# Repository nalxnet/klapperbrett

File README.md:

# klapperbrett

Die Klappenanzeige (Salzkotten EC2000-FP6) stammt aus einer Zapfsäule und zeigte die üblichen Werte (Literpreis, Gesamtmenge, Gesamtpreis) an.

Es sind drei Anschlüsse vorhanden:
* Pfostenstecker 10-polig, von außen zugänglich: vmtl. Anschluss an den Rest der Zapfsäule, inkl. Stromversorgung (2 Pins +24V, 2 Pins GND).
* Pfostenstecker 12-polig(?), nur von innen zugänglich: vmtl. Service-Anschluss zur Neuprogrammierung, kein +24V oder +5V, nur GND.
* 2 Bohrungen für +24V und GND, nicht verlötet.

Steuerung erfolgt original über einen 8-bit Mikrocontroller, der in einen 40-pol. IC-Sockel gesteckt ist. Hier setzen wir an und ersetzen diesen mit einem Arduino/ESP.

Es gibt 3 Zeilen, die oberen beiden haben 5 Elemente, die unterste hat 4. Jedes Element hat 7 Segmente zur Anzeige einer Zahl. Logisch sind zur Ansteuerung alle Elemente in einer Reihe aufgebaut, dadurch lassen sich die einzelnen Segmente als Matrix darstellen, wobei die Elemente die Spalten und die Segmente die Zeilen darstellen. Jedes Segment besteht aus einem Elektromagneten, der je nach Stromfluss anders polarisiert ist und dadurch das Segment in An- bzw. Aus-Position bewegt. Dafür ist eine Seite der Spule direkt an die Spaltenleitung angeschlossen. Die andere Seite der Spule ist mit jeweils einer Diode an zwei Elementleitungen angeschlossen. Eine zum Bewegen in An-Position, die andere für die Aus-Position.

Die Ansteuerung der einzelnen Segmente übernehmen zwei FP2800A. Der obere (FPZ) steuert die Zeilen, der untere (FPS) die Spalten.

Pinbelegung Mikrocontroller (alle nicht aufgeführten sind unbekannt):
```
1: FPS A0
2: FPS A1
3: FPS A2
4: FPS B0
5: FPS B1
6: (über JP1 an PCF8582C-2 Pin SDA --> I2C)
7: FPS ENABLE
...
20: GND
33: FPZ ENABLE
34: FPZ B0, FPZ DATA, FPS DATA
35: FPZ B1
...
37: FPZ A2
38: FPZ A1
39: FPZ A0
40: +5V
```

Ansteuerung der Segmente erfolgt durch Setzen der Spalten- und Zeilenadresse (je 8 Bit), DATA wird durch invertierenden Schmitt-Trigger bereits passend gesetzt. Um das Segment zu schalten muss abschließend ein kurzer Puls an beiden ENABLE-Pins gleichzeitig (HIGH nach LOW) erfolgen, für dessen Zeit die Spalten- und Zeilenleitung tatsächlich gesetzt wird.

Adressierung der Elemente erfolgt von oben nach unten, von rechts nach links. Freie Element-Plätze sind ebenfalls adressiert, 8 und 16 werden übersprungen.

```
 6  5  4  3  2  1

13 12 11 10  9  7

   19 18 17 15 14
```

Die Adressierung der Segmente erfolgt gegen den Uhrzeigersinn, beginnend mit dem obersten Segment und endend mit dem mittleren Segment. 1-7 schalten das Segment aktiv, 9-15 schalten das Segment inaktiv.

Netzteil 24V, mind. 200mA
 
Pinbelegung X5? (extern)
```
...
2: +24V
3: +24V
...
5: GND
...
9: GND
...
```
 
Pinbelegung X6
 
```
... 
14: GND
15: GND
...
```
 
Pinbelegung X7
 
```
1: +24V
2: GND
```

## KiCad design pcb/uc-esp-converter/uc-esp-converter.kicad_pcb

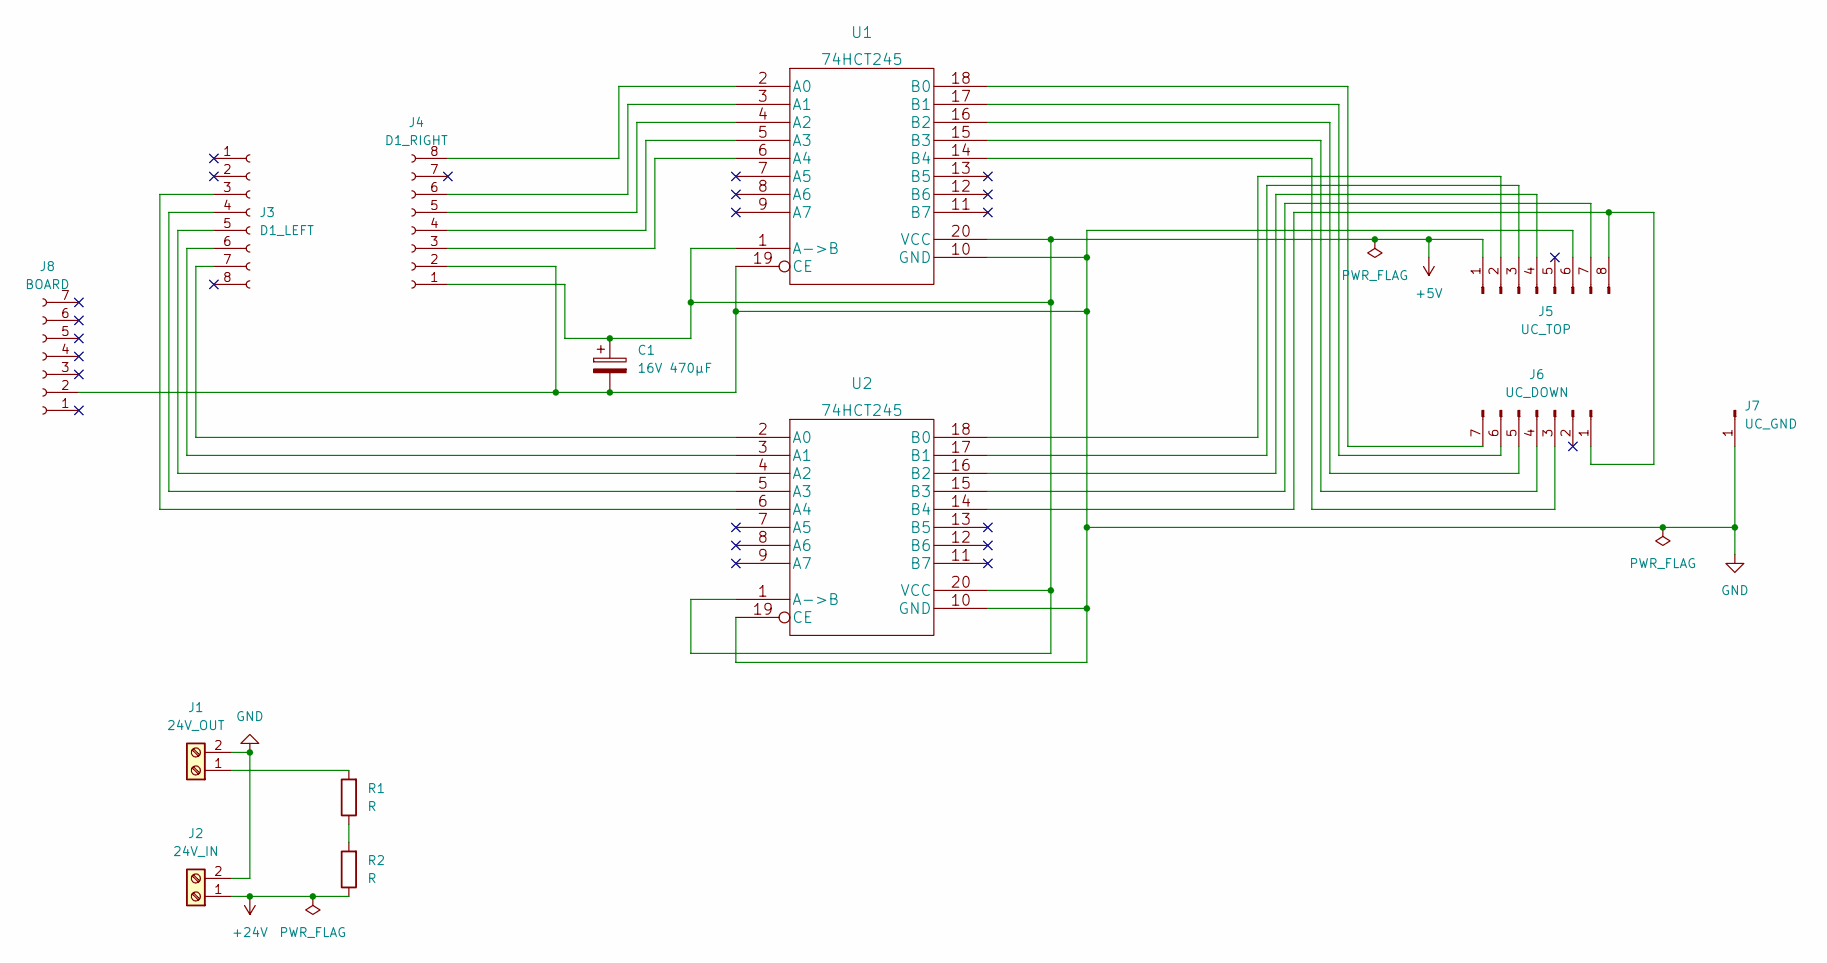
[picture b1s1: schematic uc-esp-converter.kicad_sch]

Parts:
C1: 16V 470µF; CP_Radial_D10.0mm_P5.00mm
J1: 24V_OUT; TerminalBlock_MetzConnect_Type101_RT01602HBWC_1x02_P5.08mm_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
J2: 24V_IN; TerminalBlock_MetzConnect_Type101_RT01602HBWC_1x02_P5.08mm_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
J3: D1_LEFT; PinSocket_1x08_P2.54mm_Vertical
J4: D1_RIGHT; PinSocket_1x08_P2.54mm_Vertical
J5: UC_TOP; PinHeader_1x08_P2.54mm_Vertical
J6: UC_DOWN; PinHeader_1x07_P2.54mm_Vertical
J7: UC_GND; PinHeader_1x01_P2.54mm_Vertical
J8: BOARD; PinSocket_1x07_P2.54mm_Vertical
R1, R2: R; R_Axial_DIN0207_L6.3mm_D2.5mm_P10.16mm_Horizontal
U1, U2: 74HCT245; DIP-20_W7.62mm

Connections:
+5V: C1.1, J4.1, J5.1, U1.1 (A->B), U1.20 (VCC), U2.1 (A->B), U2.20 (VCC)
+24V: J2.1, R2.1
GND: C1.2, J1.2, J2.2, J4.2, J5.6, J7.1, J8.2, U1.10 (GND), U1.19 (CE), U2.10 (GND), U2.19 (CE)
unnamed: J1.1, R1.2
unnamed: J5.2, U2.18 (B0)
unnamed: J5.3, U2.17 (B1)
unnamed: J5.4, U2.16 (B2)
unnamed: J5.7, U2.15 (B3)
unnamed: J5.8, J6.1, U2.14 (B4)
unnamed: R1.1, R2.2
unnamed: J4.8, U1.2 (A0)
unnamed: J4.6, U1.3 (A1)
unnamed: J4.5, U1.4 (A2)
unnamed: J4.4, U1.5 (A3)
unnamed: J4.3, U1.6 (A4)
unnamed: J6.3, U1.14 (B4)
unnamed: J6.4, U1.15 (B3)
unnamed: J6.5, U1.16 (B2)
unnamed: J6.6, U1.17 (B1)
unnamed: J6.7, U1.18 (B0)
unnamed: J3.7, U2.2 (A0)
unnamed: J3.6, U2.3 (A1)
unnamed: J3.5, U2.4 (A2)
unnamed: J3.4, U2.5 (A3)
unnamed: J3.3, U2.6 (A4)

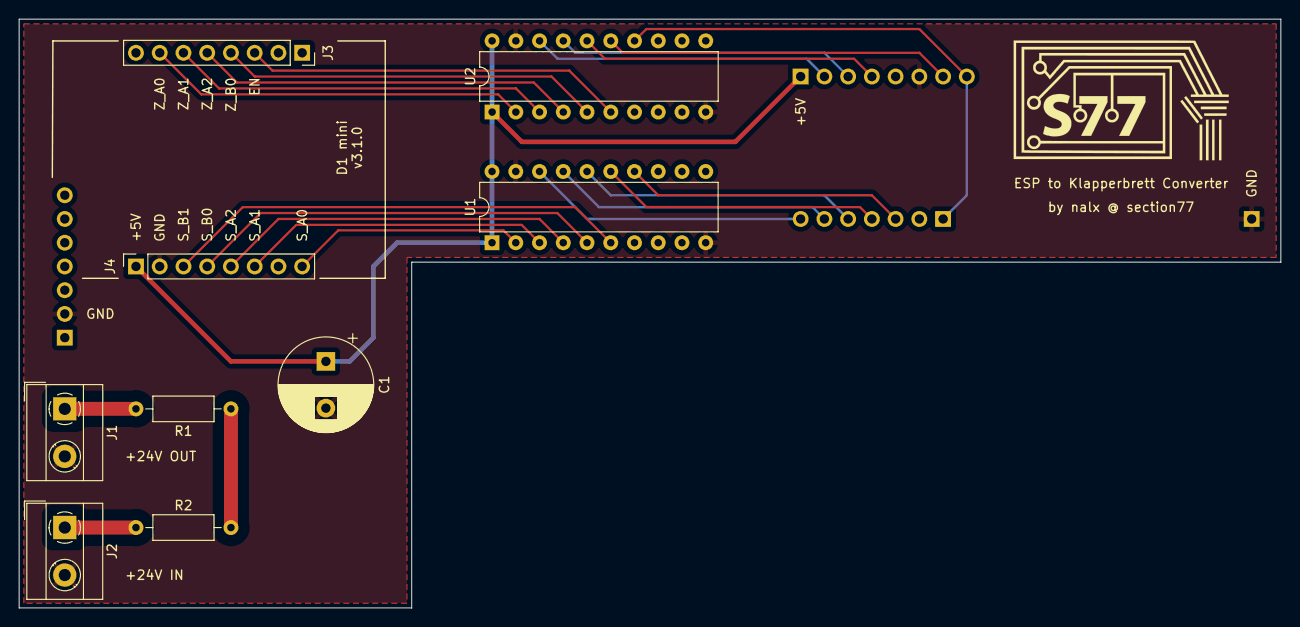
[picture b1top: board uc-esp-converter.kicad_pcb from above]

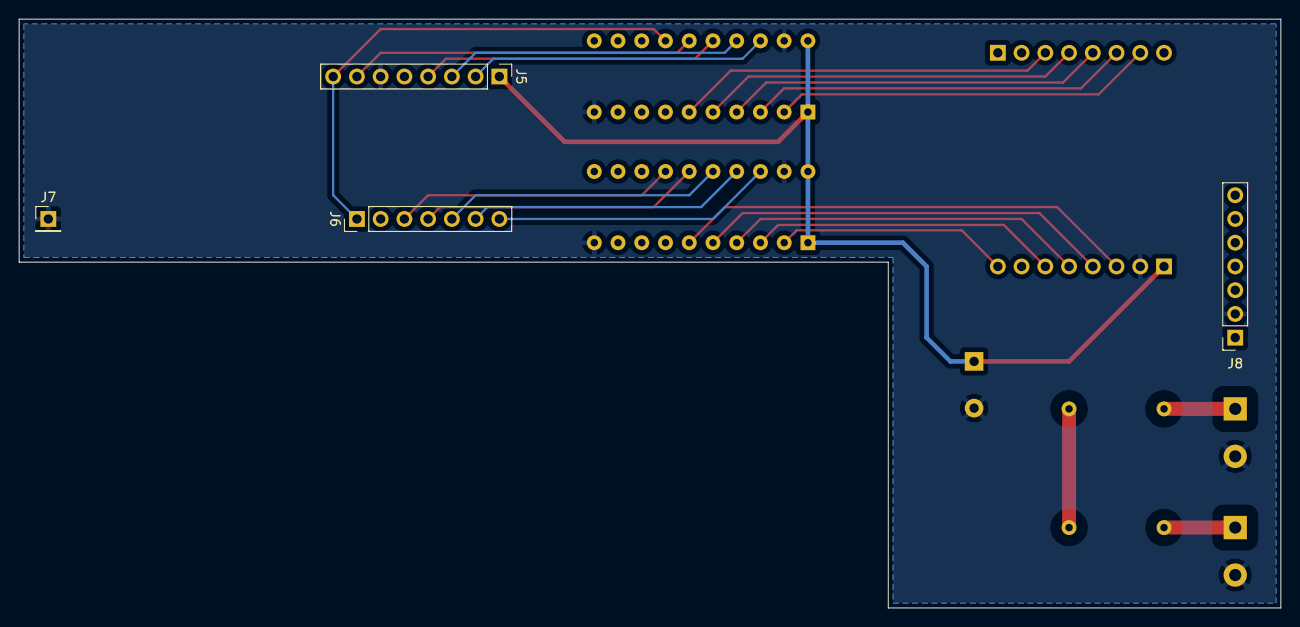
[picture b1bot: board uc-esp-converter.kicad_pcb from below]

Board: 2 copper layers, 135.0 x 63.0 mm, 14 parts (4 on the bottom side), 25 nets.

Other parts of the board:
Ref**: Val**; section77_logo_kicad

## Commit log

2018-04-03 init
2018-04-03 Spezial-Funktionen wieder erreichbar gemacht + cleanup
2022-07-19 update pin assignments to pcb layout
2022-07-19 move sketches to own folder
2022-07-19 add demo sketches
2022-07-19 add pcb files
2022-07-19 update readme with device documentation
